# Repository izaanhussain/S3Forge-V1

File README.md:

# S3Forge-V1

A custom ESP32-S3 development board designed in KiCad, featuring USB-C connectivity, GPIO expansion headers, reset and boot controls with indicator leds, and an onboard 3.3V regulator

<p align="center">

<p align="center">
  <em> render </em>
</p>

the schematic PCB layout, bill of materials, and manufacturing files are included in the repository 

## Specifications

| Specification | Details |
|---|---|
| Microcontroller module | ESP32-S3-WROOM-1 |
| PCB dimensions | 70 mm × 55 mm |
| USB connector | USB-C receptacle |
| Intended input voltage | 5V nominal via USB-C VBUS |
| Voltage regulator | AMS1117-3.3 |
| Logic voltage | 3.3V |
| GPIO expansion | Two 1×20 headers |
| Header pitch | 2.54 mm |
| Controls | Reset and Boot buttons |
| Indicators | Power LED and user LED |
| Design software | KiCad |
| Firmware | Test Firmware Included |

## Features

* ESP32-S3-WROOM-1 module footprint
* USB-C connector with USB D+ and D− signal nets
* Two 20-pin GPIO expansion headers
* Reset and Boot push buttons
* Power and user indicator LEDs
* Onboard AMS1117-3.3 voltage regulator
* Supporting capacitors and resistors
* Editable KiCad schematic and PCB layout
* Bill of materials and Gerber manufacturing archive

### Schematic

## Extra Details

### 1. PCB 

the current PCB outline is approx **70 mm × 55 mm**
The board includes footprints for the ESP32-S3 module, USB-C connector, voltage regulator, supporting components, push buttons, indicator LEDs, and two expansion headers

### 2. GPIO Expansion

The schematic includes the following labelled ESP32-S3 signals:

* IO1–IO18
* IO21
* IO35–IO47
and Two 1×20 headers with 2.54 mm pitch

### 3. Power Architecture

the power architecture here is:

1). **USB-C VBUS:** Supplies 5V input
2). **AMS1117-3.3 regulator:** used to convert the input supply to 3.3V
3). **3.3V rail:** supplies the ESP32-S3 module and other low-voltage circuitry
4). **Ground:** Common ground pin

### 4. USB-C Functionality

the schematic contains a USB-C receptacle with VBUS, GND, D+, and D− signal nets

the programming approach is to use the ESP32-S3's native USB interface . provided the final wiring and firmware configuration support it. there is no separate usb to UART 

## Bill of Materials

The complete BOM is available at [`Production/BOM.csv`](Production/BOM.csv).

| Reference | Component | Quantity |
|---|---|---:|
| U1 | ESP32-S3-WROOM-1 | 1 |
| U2 | AMS1117-3.3 regulator | 1 |
| J1 | USB-C receptacle | 1 |
| J2, J3 | 1×20 pin headers | 2 |
| SW1, SW2 | Reset and Boot switches | 2 |
| D1, D2 | Indicator LEDs | 2 |
| C1, C2 | 10 µF capacitors | 2 |
| C3 | 100 nF capacitor | 1 |
| C4 | 1 µF capacitor | 1 |
| R1, R2 | 10 kΩ resistors | 2 |
| R3, R4 | 5.1 kΩ resistors | 2 |
| R5 | 1 kΩ resistor | 1 |
| R6 | 330 Ω resistor | 1 |

## getting Started

to use a an assembled S3Forge-V1 board, you'll need:-

1) An S3Forge-V1 PCB with components soldered 
2) A proper USB-C data cable
3) A computer running Windows or any other OS
4) arduino IDE or Espressif esp-idf
5) install the USB drivers if required by your OS

### Step 1: install Arduino IDE

1. install the Arduino IDE from the official Arduino website
2. open preferences and configure the Espressif ESP32 board package using the official installation instructions
3. open Boards Manger and install the ESP32 board package
4. select ESP32S3 Dev Module from Tools -> Board -> esp32

the upload settings are:-

1)USB CDC On Boot: Enabled
2)Upload Mode: Hardware CDC and JTAG
3)USB Mode: Hardware CDC and JTAG

select the COM port that appears when you connect the board and upload the firmware

Official resources you can checkout:-
- Arduino IDE: https://www.arduino.cc/en/software
- Arduino-ESP32 documentation: https://docs.espressif.com/projects/arduino-esp32/en/latest/

### Alternative: ESP-IDF

For development with Espressif's native framework:

1). install ESP-IDF using the official guide
2). create or open an ESP-IDF example project
3). set the target to `esp32s3`.
4). configure the correct serial or USB interface for the board

Official documentation: https://docs.espressif.com/projects/esp-idf/en/stable/esp32s3/get-started/

### Step 2: Connect the Board

after verifying the assembled hardware:--

1). connect the board to your computer using a USB-C data cable
2). check the available serial devices or Windows Device Manager
3). identify the port associated with the board

if the board is not detected check the cable  USB-C wiring soldering, and native USB config

### Step 3: Upload a Sample/test Program

A basic test firmware is available in the `Firmware` folder as `test_firmware.ino`

1). open the `test_firmware.ino` file in Arduino IDE
2). select the ESP32-S3 board from the boards menu
3). connect the board using a USB data cable and selct the correct port
4). click upload and wait for it to finish

set the baud rate to 115200 to check the output from the board

if the upload fails try pressing and holding the boot button while uploading and press Reset if needed

the firmware is just a basic test for now and the board should be checked properly before connecting other components to the GPIO pins, will release the proper specs and GPIO functions after i build it successfully 

### Step 4: View Serial Output

1). open the Arduino IDE Serial Monitor or an appropriate ESP-IDF monitor
2). select the correct port
3). set the baud rate to match the sample program which is 115200 baud rate
4). reset the board and check for output 

## Repository Structure

```text
S3Forge-V1-main/
├── PCB/
│   ├── S3Forge-V1.kicad_pro
│   ├── S3Forge-V1.kicad_sch
│   └── S3Forge-V1.kicad_pcb
├── Production/
│   ├── BOM.csv
│   ├── gerbers.zip
│   ├── S3Forge-V1.kicad_pro
│   ├── S3Forge-V1.kicad_sch
│   └── S3Forge-V1.kicad_pcb
├── LICENSE
└── README.md
```

## Manufacturing Files

The `Production/` directory contains the BOM, Gerber archive, and copies of the KiCad design files.

## License

See [`LICENSE`](LICENSE) for the project's license.

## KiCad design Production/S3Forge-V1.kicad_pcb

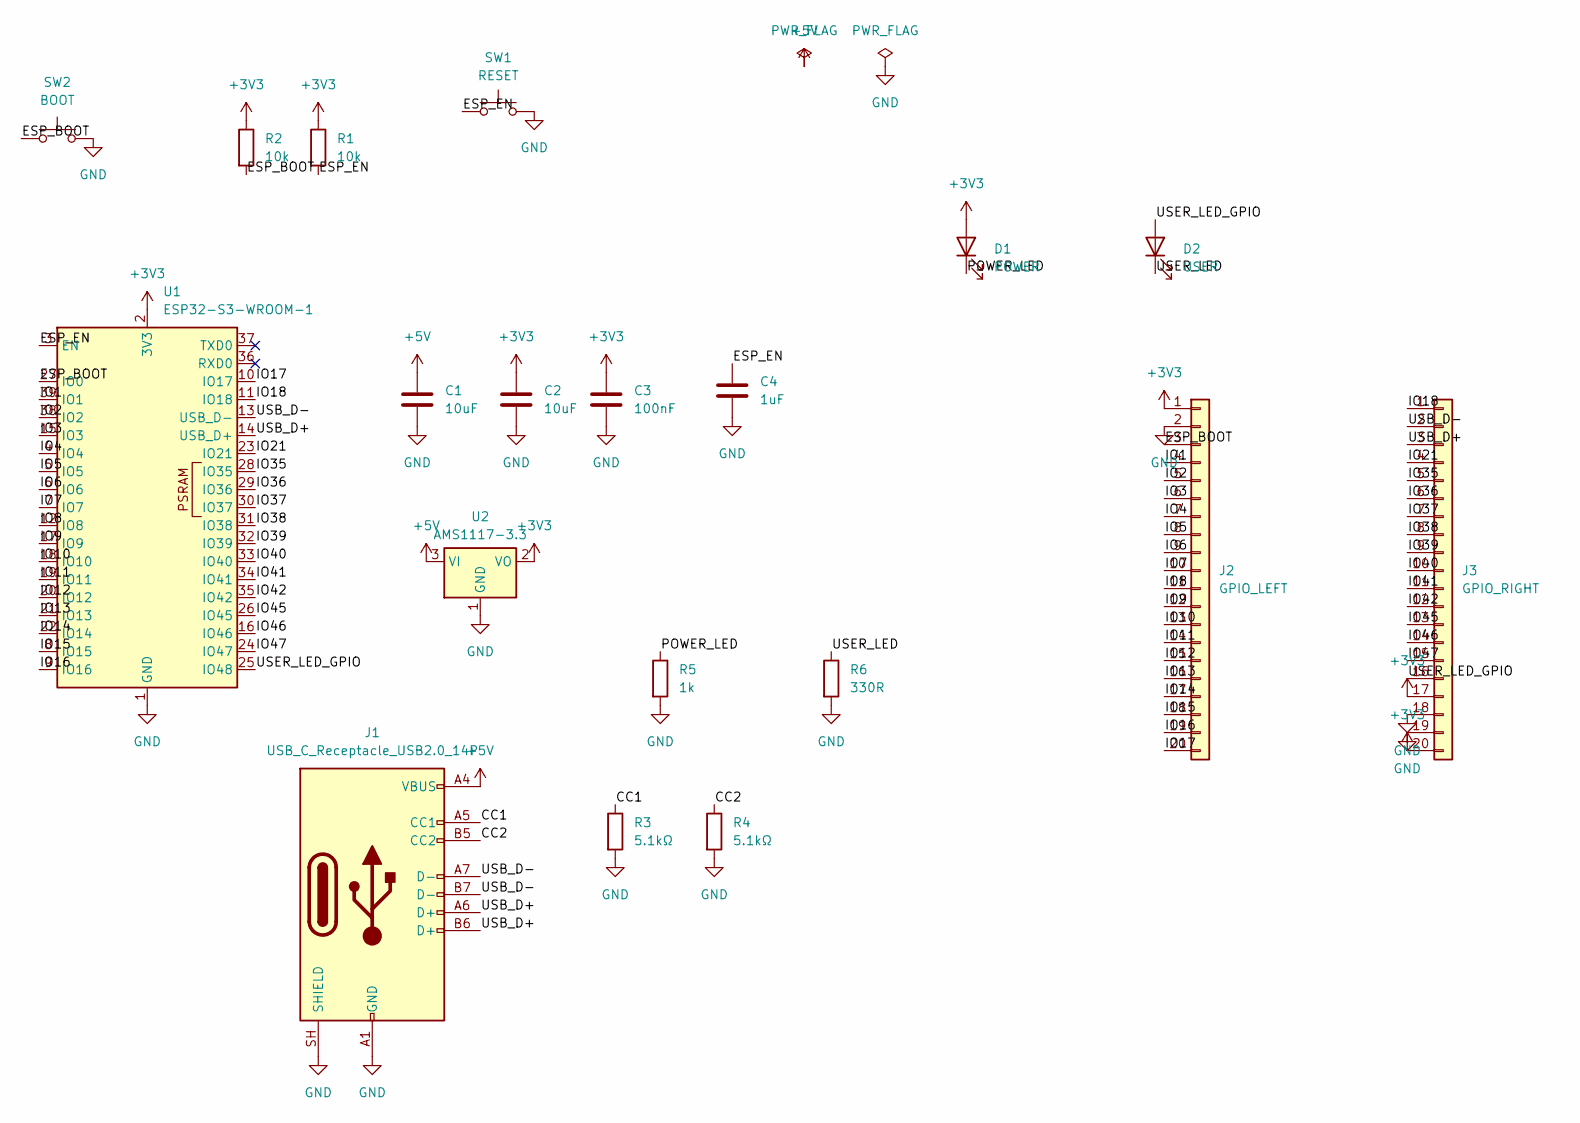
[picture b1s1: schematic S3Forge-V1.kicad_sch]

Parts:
C1, C2: 10uF; C_0805_2012Metric
C3: 100nF; C_0805_2012Metric
C4: 1uF; C_0805_2012Metric
D1: POWER; LED_0805_2012Metric
D2: USER; LED_0805_2012Metric
J1: USB_C_Receptacle_USB2.0_14P; USB_C_Receptacle_HRO_TYPE-C-31-M-12
J2: GPIO_LEFT; PinHeader_1x20_P2.54mm_Vertical
J3: GPIO_RIGHT; PinHeader_1x20_P2.54mm_Vertical
R1, R2: 10k; R_0805_2012Metric
R3, R4: 5.1kΩ; R_0805_2012Metric
R5: 1k; R_0805_2012Metric
R6: 330R; R_0805_2012Metric
SW1: RESET; SW_NKK_GW12LJP
SW2: BOOT; SW_NKK_GW12LJP
U1: ESP32-S3-WROOM-1
U2: AMS1117-3.3; SOT-223-3_TabPin2

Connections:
+3V3: C2.1, C3.1, D1.2 (A), J2.1, J3.17, J3.20, R1.1, R2.1, U1.2 (3V3), U2.2 (VO)
+5V: C1.1, J1.A4 (VBUS), J1.A9 (VBUS), J1.B4 (VBUS), J1.B9 (VBUS), U2.3 (VI)
/CC1: J1.A5 (CC1), R3.1
/CC2: J1.B5 (CC2), R4.1
/ESP_BOOT: J2.3, R2.2, SW2.1, U1.27 (IO0)
/ESP_EN: C4.1, R1.2, SW1.1, U1.3 (EN)
/IO1: J2.4, U1.39 (IO1)
/IO2: J2.5, U1.38 (IO2)
/IO3: J2.6, U1.15 (IO3)
/IO4: J2.7, U1.4 (IO4)
/IO5: J2.8, U1.5 (IO5)
/IO6: J2.9, U1.6 (IO6)
/IO7: J2.10, U1.7 (IO7)
/IO8: J2.11, U1.12 (IO8)
/IO9: J2.12, U1.17 (IO9)
/IO10: J2.13, U1.18 (IO10)
/IO11: J2.14, U1.19 (IO11)
/IO12: J2.15, U1.20 (IO12)
/IO13: J2.16, U1.21 (IO13)
/IO14: J2.17, U1.22 (IO14)
/IO15: J2.18, U1.8 (IO15)
/IO16: J2.19, U1.9 (IO16)
/IO17: J2.20, U1.10 (IO17)
/IO18: J3.1, U1.11 (IO18)
/IO21: J3.4, U1.23 (IO21)
/IO35: J3.5, U1.28 (IO35)
/IO36: J3.6, U1.29 (IO36)
/IO37: J3.7, U1.30 (IO37)
/IO38: J3.8, U1.31 (IO38)
/IO39: J3.9, U1.32 (IO39)
/IO40: J3.10, U1.33 (IO40)
/IO41: J3.11, U1.34 (IO41)
/IO42: J3.12, U1.35 (IO42)
/IO45: J3.13, U1.26 (IO45)
/IO46: J3.14, U1.16 (IO46)
/IO47: J3.15, U1.24 (IO47)
/POWER_LED: D1.1 (K), R5.1
/USB_D+: J1.A6 (D+), J1.B6 (D+), J3.3, U1.14 (USB_D+)
/USB_D-: J1.A7 (D-), J1.B7 (D-), J3.2, U1.13 (USB_D-)
/USER_LED: D2.1 (K), R6.1
/USER_LED_GPIO: D2.2 (A), J3.16, U1.25 (IO48)
GND: C1.2, C2.2, C3.2, C4.2, J1.A1 (GND), J1.A12 (GND), J1.B1 (GND), J1.B12 (GND), J1.SH (SHIELD), J2.2, J3.18, J3.19, R3.2, R4.2, R5.2, R6.2, SW1.2, SW2.2, U1.1 (GND), U1.40 (GND), U1.41 (GND), U2.1 (GND)

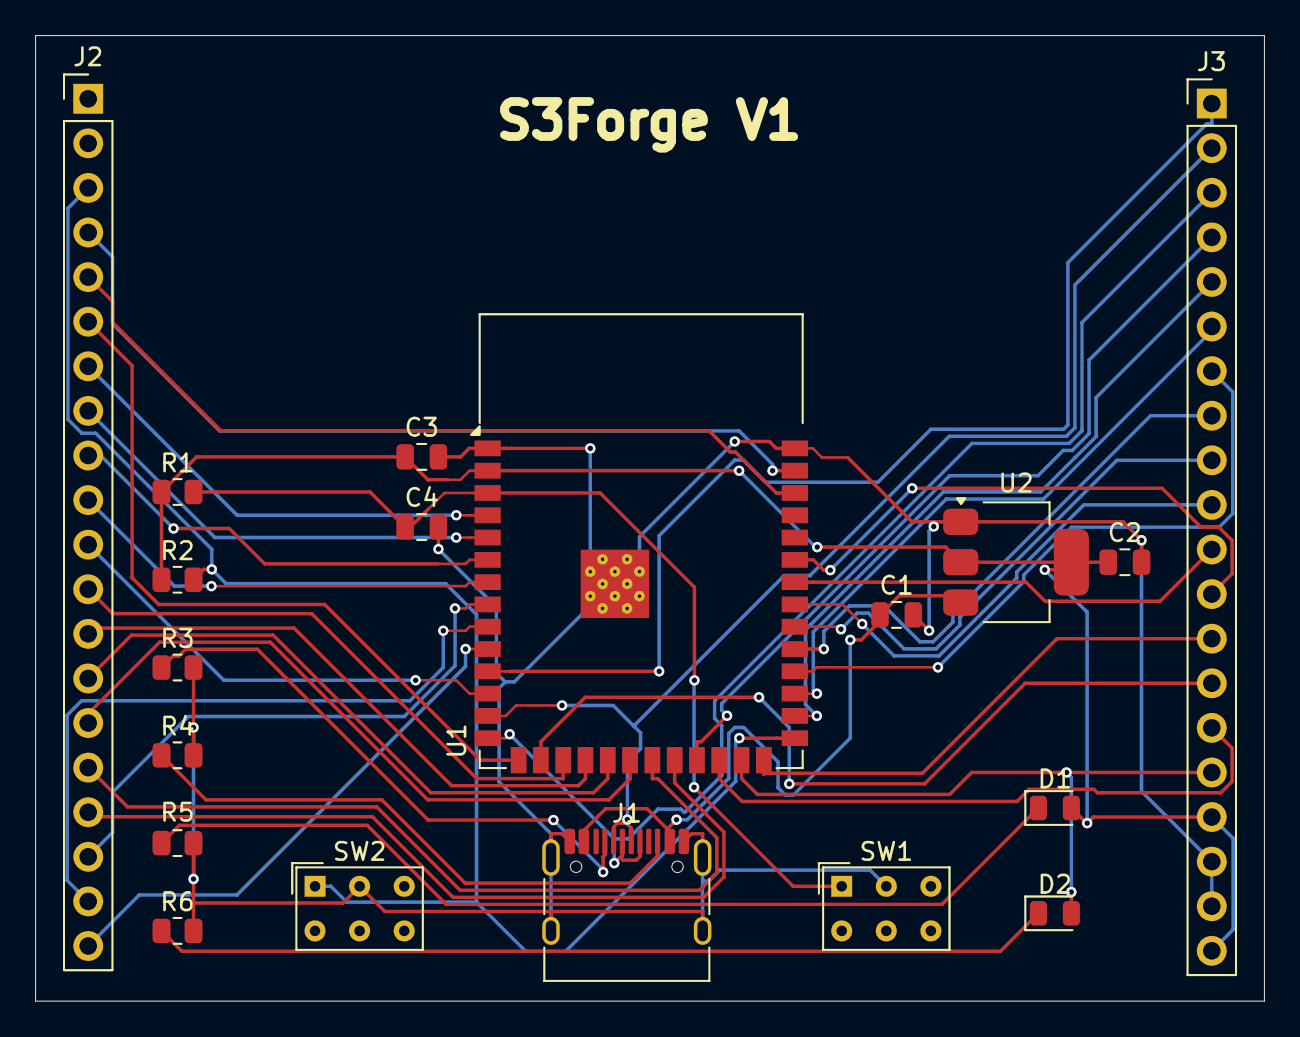
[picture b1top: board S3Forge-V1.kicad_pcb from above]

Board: 2 copper layers, 70.0 x 55.0 mm, 19 parts (0 on the bottom side), 42 nets.

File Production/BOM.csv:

Reference,Quantity,Value / Part,Footprint,Description,Notes
U1,1,ESP32-S3-WROOM-1,RF_Module:ESP32-S3-WROOM-1,ESP32-S3 wireless module,Confirm exact module variant before ordering
U2,1,AMS1117-3.3,Package_TO_SOT_SMD:SOT-223-3_TabPin2,3.3 V linear voltage regulator,Verify footprint pinout against exact part
J1,1,USB-C receptacle,Connector_USB:USB_C_Receptacle_HRO_TYPE-C-31-M-12,USB 2.0 USB-C connector,Check exact connector footprint and pin mapping
"J2, J3",2,"1x20, 2.54 mm pin header",Connector_PinHeader_2.54mm:PinHeader_1x20_P2.54mm_Vertical,GPIO expansion headers,Male/female style depends on assembly choice
"SW1, SW2",2,NKK GW12LJP,Button_Switch_THT:NKK_GW12LJP,Reset and Boot switches,Confirm footprint and switch availability
"C1, C2",2,10 uF,Capacitor_SMD:C_0805_2012Metric,SMD capacitor,Voltage rating and dielectric not specified
C3,1,100 nF,Capacitor_SMD:C_0805_2012Metric,SMD decoupling capacitor,Voltage rating and dielectric not specified
C4,1,1 uF,Capacitor_SMD:C_0805_2012Metric,SMD capacitor,Voltage rating and dielectric not specified
"R1, R2",2,10 kOhm,Resistor_SMD:R_0805_2012Metric,SMD resistor,Tolerance and power rating not specified
"R3, R4",2,5.1 kOhm,Resistor_SMD:R_0805_2012Metric,SMD resistor,Tolerance and power rating not specified
R5,1,1 kOhm,Resistor_SMD:R_0805_2012Metric,SMD resistor,Tolerance and power rating not specified
R6,1,330 Ohm,Resistor_SMD:R_0805_2012Metric,SMD resistor,Tolerance and power rating not specified
D1,1,POWER LED,LED_SMD:LED_0805_2012Metric,Power indicator LED,LED colour and polarity to be confirmed
D2,1,USER LED,LED_SMD:LED_0805_2012Metric,User indicator LED,LED colour and polarity to be confirmed
